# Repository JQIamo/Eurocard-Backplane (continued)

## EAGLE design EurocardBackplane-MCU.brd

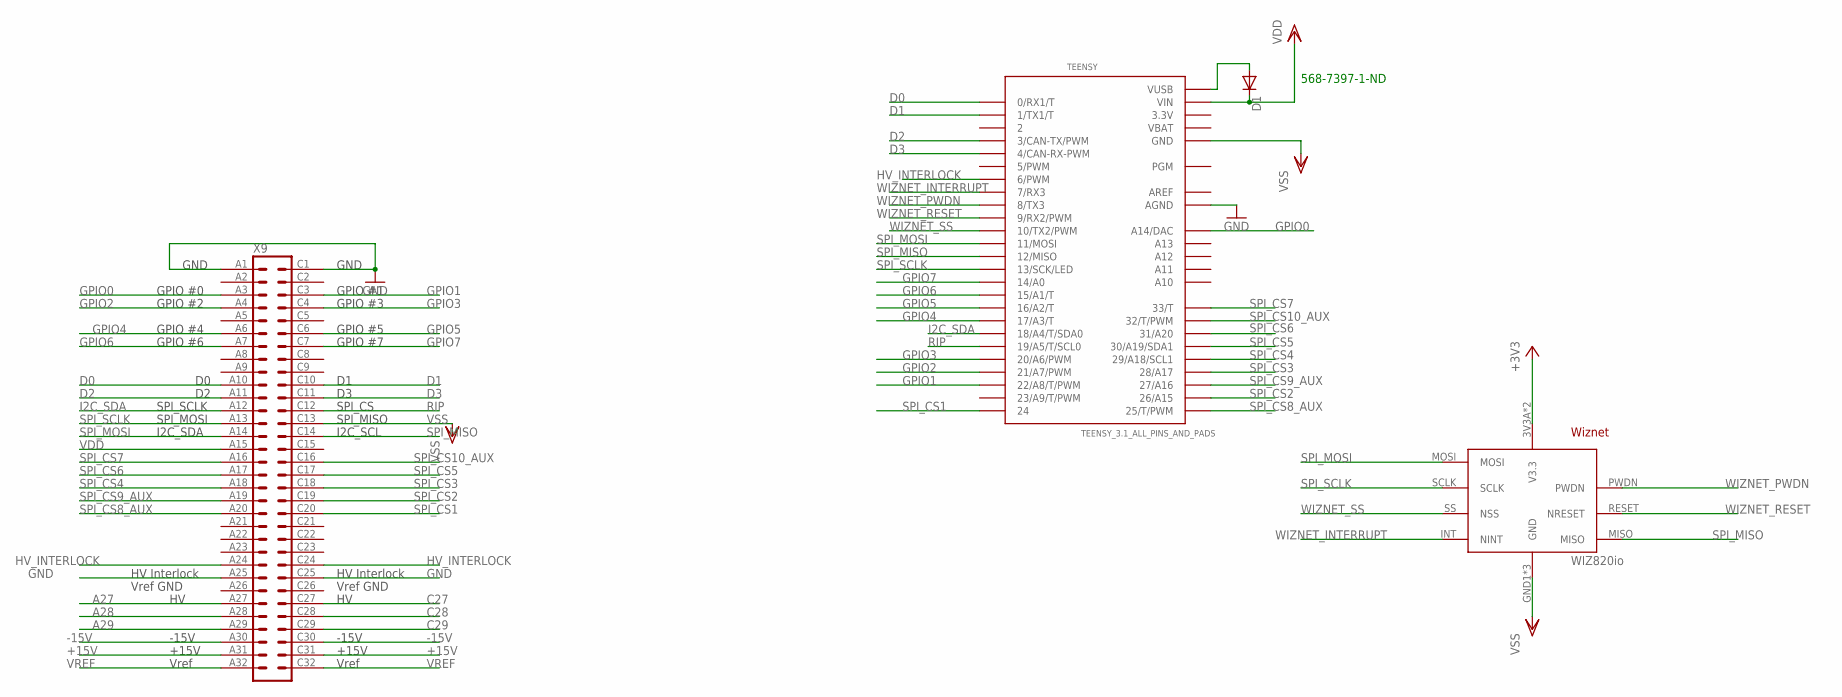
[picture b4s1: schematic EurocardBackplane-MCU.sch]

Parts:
D1: DIODE-SOD523; SOD523
TEENSY: TEENSY_3.1_ALL_PINS_AND_PADS; TEENSY_3.1_ALLPINS
U2: WIZ820IO; WIZNET
X9: VG64-PLAIN

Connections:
3.3V: TEENSY.3.3V, TEENSY.3.3V1 (3.3V), TEENSY.3.3V2 (3.3V)
+3V3: U2.3V3A (V3.3), U2.3V3B (V3.3)
+15V: X9.A31, X9.C31
-15V: X9.A30, X9.C30
A27: X9.A27
A28: X9.A28
A29: X9.A29
AREF: TEENSY.AREF
C27: X9.C27
C28: X9.C28
C29: X9.C29
D0: TEENSY.0 (0/RX1/T), X9.A10
D1: TEENSY.1 (1/TX1/T), X9.C10
D2: TEENSY.3 (3/CAN-TX/PWM), X9.A11
D3: TEENSY.4 (4/CAN-RX-PWM), X9.C11
GND: TEENSY.AGND, X9.A1, X9.A25, X9.C1, X9.C25
GPIO0: TEENSY.A14 (A14/DAC), X9.A3
GPIO1: TEENSY.22/A8 (22/A8/T/PWM), X9.C3
GPIO2: TEENSY.21/A7 (21/A7/PWM), X9.A4
GPIO3: TEENSY.20/A6 (20/A6/PWM), X9.C4
GPIO4: TEENSY.17/A3 (17/A3/T), X9.A6
GPIO5: TEENSY.16/A2 (16/A2/T), X9.C6
GPIO6: TEENSY.15/A1 (15/A1/T), X9.A7
GPIO7: TEENSY.14/A0, X9.C7
HV_INTERLOCK: TEENSY.6 (6/PWM), X9.A24, X9.C24
I2C_SDA: TEENSY.18/A4 (18/A4/T/SDA0), X9.A12
unnamed: D1.A, TEENSY.VUSB
RIP: TEENSY.19/A5 (19/A5/T/SCL0), X9.C12
SPI_CS1: TEENSY.24, X9.C20
SPI_CS2: TEENSY.26 (26/A15), X9.C19
SPI_CS3: TEENSY.28 (28/A17), X9.C18
SPI_CS4: TEENSY.29 (29/A18/SCL1), X9.A18
SPI_CS5: TEENSY.30 (30/A19/SDA1), X9.C17
SPI_CS6: TEENSY.31 (31/A20), X9.A17
SPI_CS7: TEENSY.33 (33/T), X9.A16
SPI_CS8_AUX: TEENSY.25 (25/T/PWM), X9.A20
SPI_CS9_AUX: TEENSY.27 (27/A16), X9.A19
SPI_CS10_AUX: TEENSY.32 (32/T/PWM), X9.C16
SPI_MISO: TEENSY.12 (12/MISO), U2.MISO, X9.C14
SPI_MOSI: TEENSY.11 (11/MOSI), U2.MOSI, X9.A14
SPI_SCLK: TEENSY.13 (13/SCK/LED), U2.SCLK, X9.A13
VBAT: TEENSY.VBAT
VDD: D1.C, TEENSY.VIN, X9.A15
VREF: X9.A32, X9.C32
VSS: TEENSY.GND, TEENSY.GND1 (GND), TEENSY.GND2 (GND), U2.GND1 (GND), U2.GND2 (GND), U2.GND3 (GND), X9.C13
WIZNET_INTERRUPT: TEENSY.7 (7/RX3), U2.INT (NINT)
WIZNET_PWDN: TEENSY.8 (8/TX3), U2.PWDN
WIZNET_RESET: TEENSY.9 (9/RX2/PWM), U2.RESET (NRESET)
WIZNET_SS: TEENSY.10 (10/TX2/PWM), U2.SS (NSS)

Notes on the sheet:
568-7397-1-ND

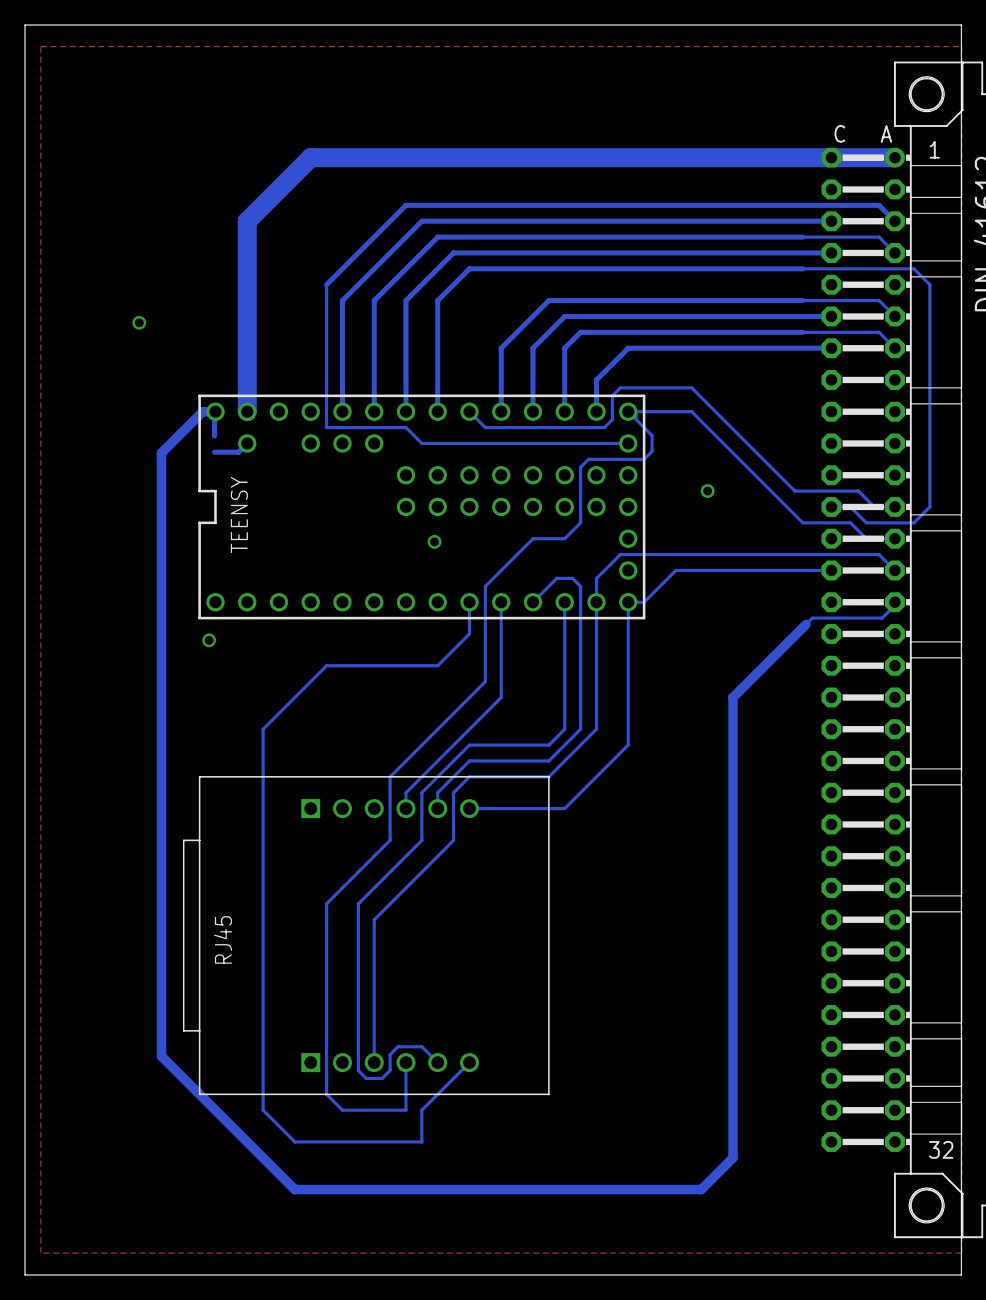
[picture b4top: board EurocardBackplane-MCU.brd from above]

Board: 2 copper layers, 74.9 x 100.0 mm, 4 parts (1 on the bottom side), 41 nets.

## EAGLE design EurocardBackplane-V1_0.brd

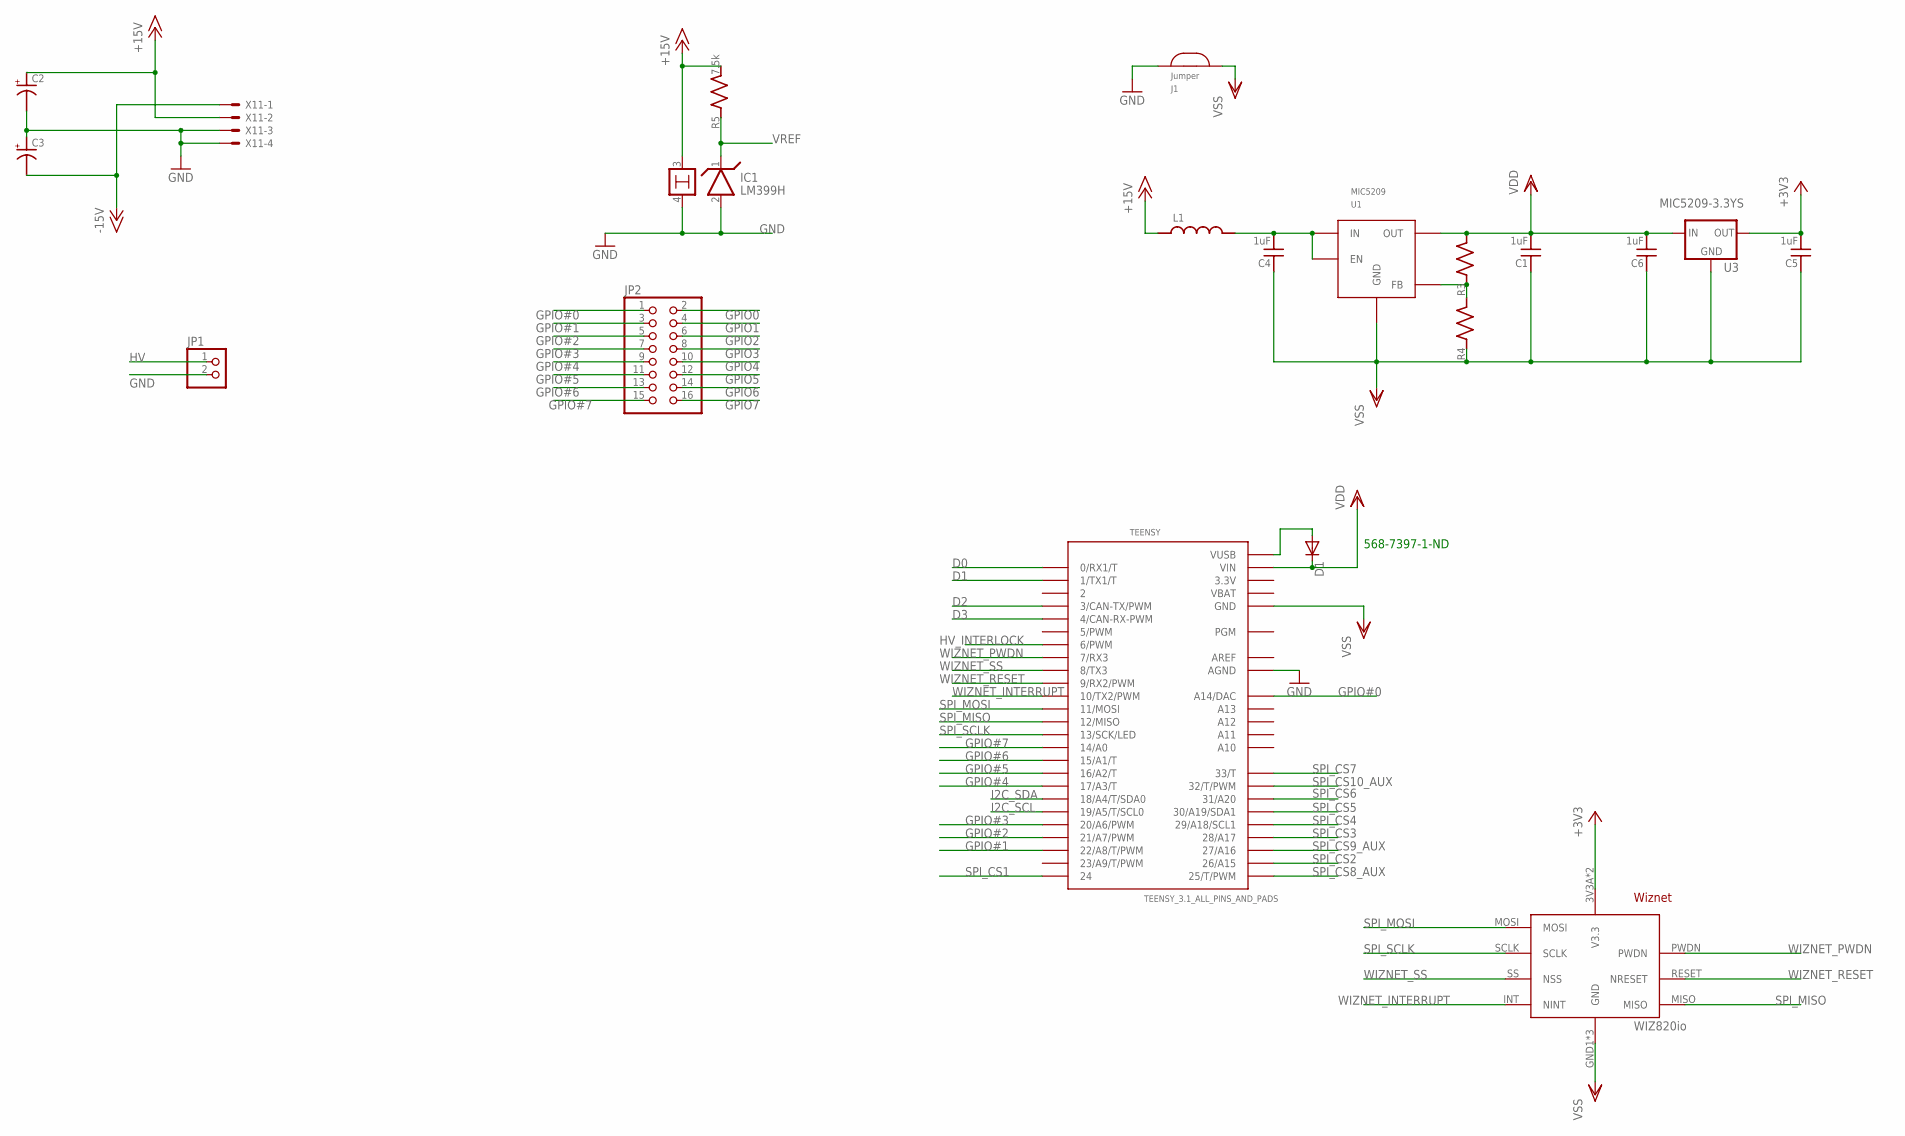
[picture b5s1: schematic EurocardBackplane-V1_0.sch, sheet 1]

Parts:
C1, C4, C5, C6: 1uF; C_MLCC_0603
C2, C3: C_POL_SMDF; PANASONIC_F
D1: DIODE-SOD523; SOD523
IC1: LM399H; TO39/4
J1: JUMPER; JUMP
JP1: PINHD-1X2; 1X02
JP2: PINHD-2X8; 2X08
L1: L_FERRITE_SMDLFERRITE_0805; R_0805
R3, R4: R_SMDR0603; R_0603
R5: 7.5k; R_0603
TEENSY: TEENSY_3.1_ALL_PINS_AND_PADS; TEENSY_3.1_ALLPINS
U1: MIC5209; TO263-5
U2: WIZ820IO; WIZNET
U3: MIC5209-3.3YS; SOT223-S
X11: 5566-4

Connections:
3.3V: TEENSY.3.3V, TEENSY.3.3V1 (3.3V), TEENSY.3.3V2 (3.3V)
+3V3: C5.P$2 (2), U2.3V3A (V3.3), U2.3V3B (V3.3), U3.3 (OUT)
+15V: C2.+, IC1.3, L1.P$1 (1), R5.P$2 (2), X11.2; also elsewhere on the board
-15V: C3.-, X11.1; also elsewhere on the board
AREF: TEENSY.AREF
D0: TEENSY.0 (0/RX1/T); also elsewhere on the board
D1: TEENSY.1 (1/TX1/T); also elsewhere on the board
D2: TEENSY.3 (3/CAN-TX/PWM); also elsewhere on the board
D3: TEENSY.4 (4/CAN-RX-PWM); also elsewhere on the board
GND: C2.-, C3.+, IC1.2, IC1.4, J1.P$2, JP1.2, TEENSY.AGND, X11.3, X11.4; also elsewhere on the board
GPIO0: JP2.2; also elsewhere on the board
GPIO1: JP2.4; also elsewhere on the board
GPIO2: JP2.6; also elsewhere on the board
GPIO3: JP2.8; also elsewhere on the board
GPIO4: JP2.10; also elsewhere on the board
GPIO5: JP2.12; also elsewhere on the board
GPIO6: JP2.14; also elsewhere on the board
GPIO7: JP2.16; also elsewhere on the board
GPIO#0: JP2.1, TEENSY.A14 (A14/DAC)
GPIO#1: JP2.3, TEENSY.22/A8 (22/A8/T/PWM)
GPIO#2: JP2.5, TEENSY.21/A7 (21/A7/PWM)
GPIO#3: JP2.7, TEENSY.20/A6 (20/A6/PWM)
GPIO#4: JP2.9, TEENSY.17/A3 (17/A3/T)
GPIO#5: JP2.11, TEENSY.16/A2 (16/A2/T)
GPIO#6: JP2.13, TEENSY.15/A1 (15/A1/T)
GPIO#7: JP2.15, TEENSY.14/A0
HV: JP1.1; also elsewhere on the board
HV_INTERLOCK: TEENSY.6 (6/PWM); also elsewhere on the board
I2C_SCL: TEENSY.19/A5 (19/A5/T/SCL0); also elsewhere on the board
I2C_SDA: TEENSY.18/A4 (18/A4/T/SDA0); also elsewhere on the board
unnamed: C4.P$2 (2), L1.P$2 (2), U1.1 (EN), U1.2 (IN)
unnamed: D1.A, TEENSY.VUSB
unnamed: R3.P$1 (1), R4.P$2 (2), U1.5 (FB)
SPI_CS1: TEENSY.24; also elsewhere on the board
SPI_CS2: TEENSY.26 (26/A15); also elsewhere on the board
SPI_CS3: TEENSY.28 (28/A17); also elsewhere on the board
SPI_CS4: TEENSY.29 (29/A18/SCL1); also elsewhere on the board
SPI_CS5: TEENSY.30 (30/A19/SDA1); also elsewhere on the board
SPI_CS6: TEENSY.31 (31/A20); also elsewhere on the board
SPI_CS7: TEENSY.33 (33/T); also elsewhere on the board
SPI_CS8_AUX: TEENSY.25 (25/T/PWM); also elsewhere on the board
SPI_CS9_AUX: TEENSY.27 (27/A16); also elsewhere on the board
SPI_CS10_AUX: TEENSY.32 (32/T/PWM); also elsewhere on the board
SPI_MISO: TEENSY.12 (12/MISO), U2.MISO; also elsewhere on the board
SPI_MOSI: TEENSY.11 (11/MOSI), U2.MOSI; also elsewhere on the board
SPI_SCLK: TEENSY.13 (13/SCK/LED), U2.SCLK; also elsewhere on the board
VBAT: TEENSY.VBAT
VDD: C1.P$2 (2), C6.P$2 (2), D1.C, R3.P$2 (2), TEENSY.VIN, U1.4 (OUT), U3.1 (IN)
VREF: IC1.1, R5.P$1 (1); also elsewhere on the board
VSS: C1.P$1 (1), C4.P$1 (1), C5.P$1 (1), C6.P$1 (1), J1.P$1, R4.P$1 (1), TEENSY.GND, TEENSY.GND1 (GND), TEENSY.GND2 (GND), U1.3 (GND), U1.6 (GND), U2.GND1 (GND), U2.GND2 (GND), U2.GND3 (GND), U3.2 (GND), U3.4 (GND)
WIZNET_INTERRUPT: TEENSY.10 (10/TX2/PWM), U2.INT (NINT)
WIZNET_PWDN: TEENSY.7 (7/RX3), U2.PWDN
WIZNET_RESET: TEENSY.9 (9/RX2/PWM), U2.RESET (NRESET)
WIZNET_SS: TEENSY.8 (8/TX3), U2.SS (NSS)

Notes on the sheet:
568-7397-1-ND

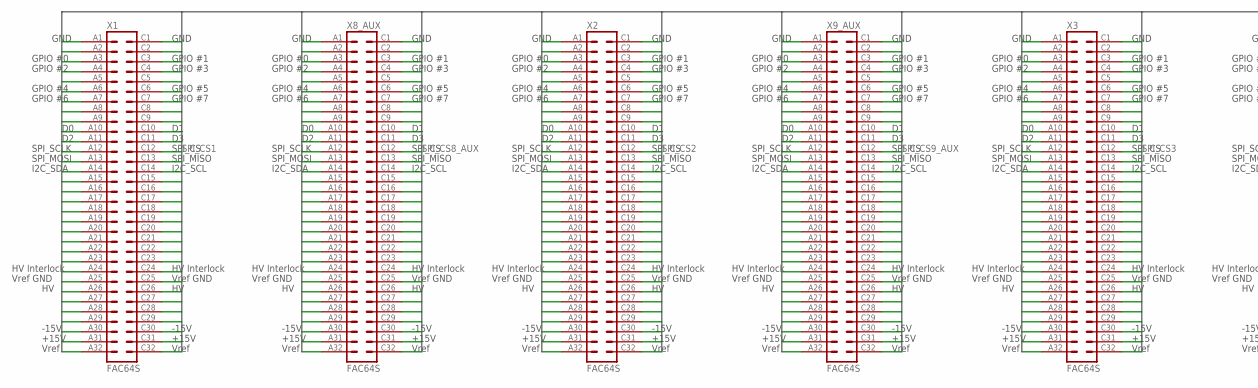
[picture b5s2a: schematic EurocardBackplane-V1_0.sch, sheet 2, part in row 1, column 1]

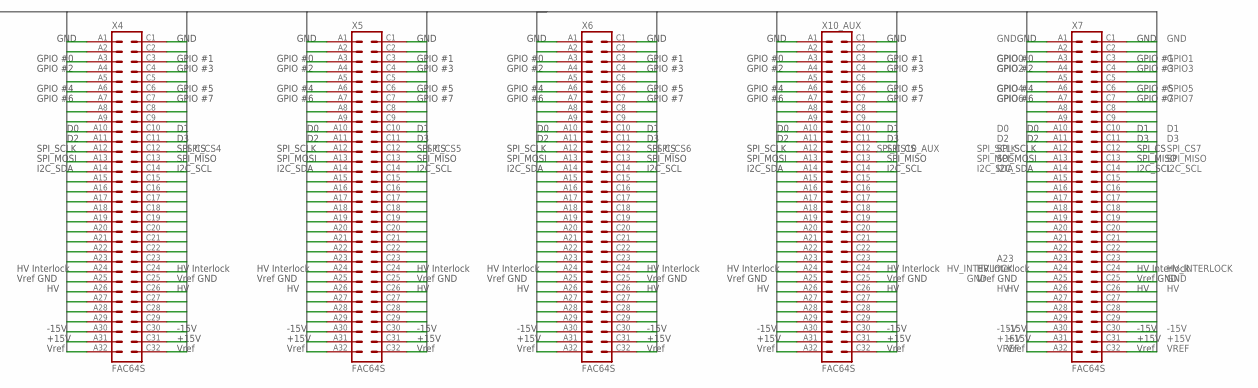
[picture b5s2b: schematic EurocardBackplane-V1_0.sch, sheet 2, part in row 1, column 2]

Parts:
X1, X2, X3, X4, X5, X6, X7, X8_AUX, X9_AUX, X10_AUX: FAC64S

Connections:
+15V: X1.A31, X1.C31, X2.A31, X2.C31, X3.A31, X3.C31, X4.A31, X4.C31, X5.A31, X5.C31, X6.A31, X6.C31, X7.A31, X7.C31, X8_AUX.A31, X8_AUX.C31, X9_AUX.A31, X9_AUX.C31, X10_AUX.A31, X10_AUX.C31; also elsewhere on the board
-15V: X1.A30, X1.C30, X2.A30, X2.C30, X3.A30, X3.C30, X4.A30, X4.C30, X5.A30, X5.C30, X6.A30, X6.C30, X7.A30, X7.C30, X8_AUX.A30, X8_AUX.C30, X9_AUX.A30, X9_AUX.C30, X10_AUX.A30, X10_AUX.C30; also elsewhere on the board
A2: X1.A2, X2.A2, X3.A2, X4.A2, X5.A2, X6.A2, X7.A2, X8_AUX.A2, X9_AUX.A2, X10_AUX.A2
A5: X1.A5, X2.A5, X3.A5, X4.A5, X5.A5, X6.A5, X7.A5, X8_AUX.A5, X9_AUX.A5, X10_AUX.A5
A8: X1.A8, X2.A8, X3.A8, X4.A8, X5.A8, X6.A8, X7.A8, X8_AUX.A8, X9_AUX.A8, X10_AUX.A8
A9: X1.A9, X2.A9, X3.A9, X4.A9, X5.A9, X6.A9, X7.A9, X8_AUX.A9, X9_AUX.A9, X10_AUX.A9
A15: X1.A15, X2.A15, X3.A15, X4.A15, X5.A15, X6.A15, X7.A15, X8_AUX.A15, X9_AUX.A15, X10_AUX.A15
A16: X1.A16, X2.A16, X3.A16, X4.A16, X5.A16, X6.A16, X7.A16, X8_AUX.A16, X9_AUX.A16, X10_AUX.A16
A17: X1.A17, X2.A17, X3.A17, X4.A17, X5.A17, X6.A17, X7.A17, X8_AUX.A17, X9_AUX.A17, X10_AUX.A17
A18: X1.A18, X2.A18, X3.A18, X4.A18, X5.A18, X6.A18, X7.A18, X8_AUX.A18, X9_AUX.A18, X10_AUX.A18
A19: X1.A19, X2.A19, X3.A19, X4.A19, X5.A19, X6.A19, X7.A19, X8_AUX.A19, X9_AUX.A19, X10_AUX.A19
A20: X1.A20, X2.A20, X3.A20, X4.A20, X5.A20, X6.A20, X7.A20, X8_AUX.A20, X9_AUX.A20, X10_AUX.A20
A21: X1.A21, X2.A21, X3.A21, X4.A21, X5.A21, X6.A21, X7.A21, X8_AUX.A21, X9_AUX.A21, X10_AUX.A21
A22: X1.A22, X2.A22, X3.A22, X4.A22, X5.A22, X6.A22, X7.A22, X8_AUX.A22, X9_AUX.A22, X10_AUX.A22
A23: X1.A23, X2.A23, X3.A23, X4.A23, X5.A23, X6.A23, X7.A23, X8_AUX.A23, X9_AUX.A23, X10_AUX.A23
A27: X1.A27, X2.A27, X3.A27, X4.A27, X5.A27, X6.A27, X7.A27, X8_AUX.A27, X9_AUX.A27, X10_AUX.A27
A28: X1.A28, X2.A28, X3.A28, X4.A28, X5.A28, X6.A28, X7.A28, X8_AUX.A28, X9_AUX.A28, X10_AUX.A28
A29: X1.A29, X2.A29, X3.A29, X4.A29, X5.A29, X6.A29, X7.A29, X8_AUX.A29, X9_AUX.A29, X10_AUX.A29
C2: X1.C2, X2.C2, X3.C2, X4.C2, X5.C2, X6.C2, X7.C2, X8_AUX.C2, X9_AUX.C2, X10_AUX.C2
C5: X1.C5, X2.C5, X3.C5, X4.C5, X5.C5, X6.C5, X7.C5, X8_AUX.C5, X9_AUX.C5, X10_AUX.C5
C8: X1.C8, X2.C8, X3.C8, X4.C8, X5.C8, X6.C8, X7.C8, X8_AUX.C8, X9_AUX.C8, X10_AUX.C8
C9: X1.C9, X2.C9, X3.C9, X4.C9, X5.C9, X6.C9, X7.C9, X8_AUX.C9, X9_AUX.C9, X10_AUX.C9
C15: X1.C15, X2.C15, X3.C15, X4.C15, X5.C15, X6.C15, X7.C15, X8_AUX.C15, X9_AUX.C15, X10_AUX.C15
C16: X1.C16, X2.C16, X3.C16, X4.C16, X5.C16, X6.C16, X7.C16, X8_AUX.C16, X9_AUX.C16, X10_AUX.C16
C17: X1.C17, X2.C17, X3.C17, X4.C17, X5.C17, X6.C17, X7.C17, X8_AUX.C17, X9_AUX.C17, X10_AUX.C17
C18: X1.C18, X2.C18, X3.C18, X4.C18, X5.C18, X6.C18, X7.C18, X8_AUX.C18, X9_AUX.C18, X10_AUX.C18
C19: X1.C19, X2.C19, X3.C19, X4.C19, X5.C19, X6.C19, X7.C19, X8_AUX.C19, X9_AUX.C19, X10_AUX.C19
C20: X1.C20, X2.C20, X3.C20, X4.C20, X5.C20, X6.C20, X7.C20, X8_AUX.C20, X9_AUX.C20, X10_AUX.C20
C21: X1.C21, X2.C21, X3.C21, X4.C21, X5.C21, X6.C21, X7.C21, X8_AUX.C21, X9_AUX.C21, X10_AUX.C21
C22: X1.C22, X2.C22, X3.C22, X4.C22, X5.C22, X6.C22, X7.C22, X8_AUX.C22, X9_AUX.C22, X10_AUX.C22
C23: X1.C23, X2.C23, X3.C23, X4.C23, X5.C23, X6.C23, X7.C23, X8_AUX.C23, X9_AUX.C23, X10_AUX.C23
C27: X1.C27, X2.C27, X3.C27, X4.C27, X5.C27, X6.C27, X7.C27, X8_AUX.C27, X9_AUX.C27, X10_AUX.C27
C28: X1.C28, X2.C28, X3.C28, X4.C28, X5.C28, X6.C28, X7.C28, X8_AUX.C28, X9_AUX.C28, X10_AUX.C28
C29: X1.C29, X2.C29, X3.C29, X4.C29, X5.C29, X6.C29, X7.C29, X8_AUX.C29, X9_AUX.C29, X10_AUX.C29
D0: X1.A10, X2.A10, X3.A10, X4.A10, X5.A10, X6.A10, X7.A10, X8_AUX.A10, X9_AUX.A10, X10_AUX.A10; also elsewhere on the board
D1: X1.C10, X2.C10, X3.C10, X4.C10, X5.C10, X6.C10, X7.C10, X8_AUX.C10, X9_AUX.C10, X10_AUX.C10; also elsewhere on the board
D2: X1.A11, X2.A11, X3.A11, X4.A11, X5.A11, X6.A11, X7.A11, X8_AUX.A11, X9_AUX.A11, X10_AUX.A11; also elsewhere on the board
D3: X1.C11, X2.C11, X3.C11, X4.C11, X5.C11, X6.C11, X7.C11, X8_AUX.C11, X9_AUX.C11, X10_AUX.C11; also elsewhere on the board
GND: X1.A1, X1.A25, X1.C1, X1.C25, X2.A1, X2.A25, X2.C1, X2.C25, X3.A1, X3.A25, X3.C1, X3.C25, X4.A1, X4.A25, X4.C1, X4.C25, X5.A1, X5.A25, X5.C1, X5.C25, X6.A1, X6.A25, X6.C1, X6.C25, X7.A1, X7.A25, X7.C1, X7.C25, X8_AUX.A1, X8_AUX.A25, X8_AUX.C1, X8_AUX.C25, X9_AUX.A1, X9_AUX.A25, X9_AUX.C1, X9_AUX.C25, X10_AUX.A1, X10_AUX.A25, X10_AUX.C1, X10_AUX.C25; also elsewhere on the board
GPIO0: X1.A3, X2.A3, X3.A3, X4.A3, X5.A3, X6.A3, X7.A3, X8_AUX.A3, X9_AUX.A3, X10_AUX.A3; also elsewhere on the board
GPIO1: X1.C3, X2.C3, X3.C3, X4.C3, X5.C3, X6.C3, X7.C3, X8_AUX.C3, X9_AUX.C3, X10_AUX.C3; also elsewhere on the board
GPIO2: X1.A4, X2.A4, X3.A4, X4.A4, X5.A4, X6.A4, X7.A4, X8_AUX.A4, X9_AUX.A4, X10_AUX.A4; also elsewhere on the board
GPIO3: X1.C4, X2.C4, X3.C4, X4.C4, X5.C4, X6.C4, X7.C4, X8_AUX.C4, X9_AUX.C4, X10_AUX.C4; also elsewhere on the board
GPIO4: X1.A6, X2.A6, X3.A6, X4.A6, X5.A6, X6.A6, X7.A6, X8_AUX.A6, X9_AUX.A6, X10_AUX.A6; also elsewhere on the board
GPIO5: X1.C6, X2.C6, X3.C6, X4.C6, X5.C6, X6.C6, X7.C6, X8_AUX.C6, X9_AUX.C6, X10_AUX.C6; also elsewhere on the board
GPIO6: X1.A7, X2.A7, X3.A7, X4.A7, X5.A7, X6.A7, X7.A7, X8_AUX.A7, X9_AUX.A7, X10_AUX.A7; also elsewhere on the board
GPIO7: X1.C7, X2.C7, X3.C7, X4.C7, X5.C7, X6.C7, X7.C7, X8_AUX.C7, X9_AUX.C7, X10_AUX.C7; also elsewhere on the board
HV: X1.A26, X1.C26, X2.A26, X2.C26, X3.A26, X3.C26, X4.A26, X4.C26, X5.A26, X5.C26, X6.A26, X6.C26, X7.A26, X7.C26, X8_AUX.A26, X8_AUX.C26, X9_AUX.A26, X9_AUX.C26, X10_AUX.A26, X10_AUX.C26; also elsewhere on the board
HV_INTERLOCK: X1.A24, X1.C24, X2.A24, X2.C24, X3.A24, X3.C24, X4.A24, X4.C24, X5.A24, X5.C24, X6.A24, X6.C24, X7.A24, X7.C24, X8_AUX.A24, X8_AUX.C24, X9_AUX.A24, X9_AUX.C24, X10_AUX.A24, X10_AUX.C24; also elsewhere on the board
I2C_SCL: X1.C14, X2.C14, X3.C14, X4.C14, X5.C14, X6.C14, X7.C14, X8_AUX.C14, X9_AUX.C14, X10_AUX.C14; also elsewhere on the board
I2C_SDA: X1.A14, X2.A14, X3.A14, X4.A14, X5.A14, X6.A14, X7.A14, X8_AUX.A14, X9_AUX.A14, X10_AUX.A14; also elsewhere on the board
SPI_CS1: X1.C12; also elsewhere on the board
SPI_CS2: X2.C12; also elsewhere on the board
SPI_CS3: X3.C12; also elsewhere on the board
SPI_CS4: X4.C12; also elsewhere on the board
SPI_CS5: X5.C12; also elsewhere on the board
SPI_CS6: X6.C12; also elsewhere on the board
SPI_CS7: X7.C12; also elsewhere on the board
SPI_CS8_AUX: X8_AUX.C12; also elsewhere on the board
SPI_CS9_AUX: X9_AUX.C12; also elsewhere on the board
SPI_CS10_AUX: X10_AUX.C12; also elsewhere on the board
SPI_MISO: X1.C13, X2.C13, X3.C13, X4.C13, X5.C13, X6.C13, X7.C13, X8_AUX.C13, X9_AUX.C13, X10_AUX.C13; also elsewhere on the board
SPI_MOSI: X1.A13, X2.A13, X3.A13, X4.A13, X5.A13, X6.A13, X7.A13, X8_AUX.A13, X9_AUX.A13, X10_AUX.A13; also elsewhere on the board
SPI_SCLK: X1.A12, X2.A12, X3.A12, X4.A12, X5.A12, X6.A12, X7.A12, X8_AUX.A12, X9_AUX.A12, X10_AUX.A12; also elsewhere on the board
VREF: X1.A32, X1.C32, X2.A32, X2.C32, X3.A32, X3.C32, X4.A32, X4.C32, X5.A32, X5.C32, X6.A32, X6.C32, X7.A32, X7.C32, X8_AUX.A32, X8_AUX.C32, X9_AUX.A32, X9_AUX.C32, X10_AUX.A32, X10_AUX.C32; also elsewhere on the board

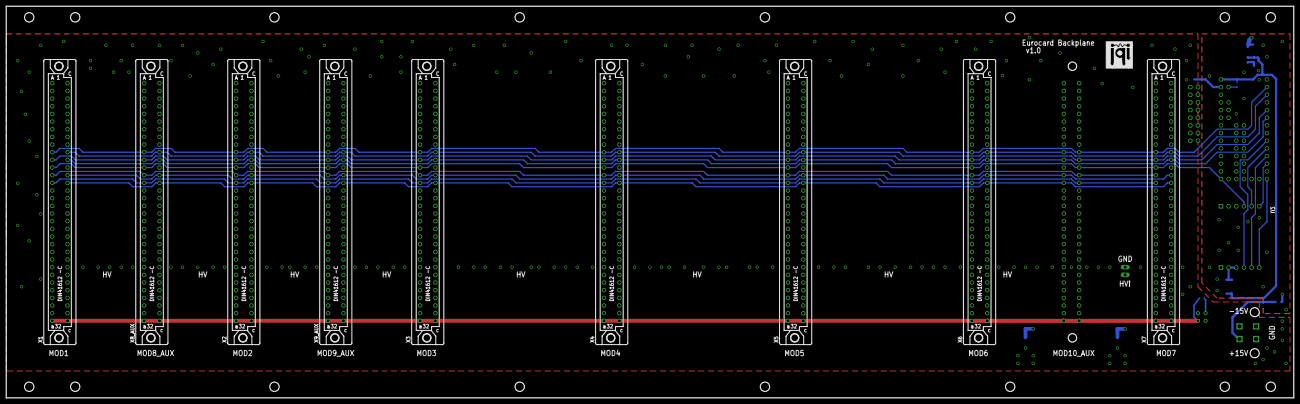
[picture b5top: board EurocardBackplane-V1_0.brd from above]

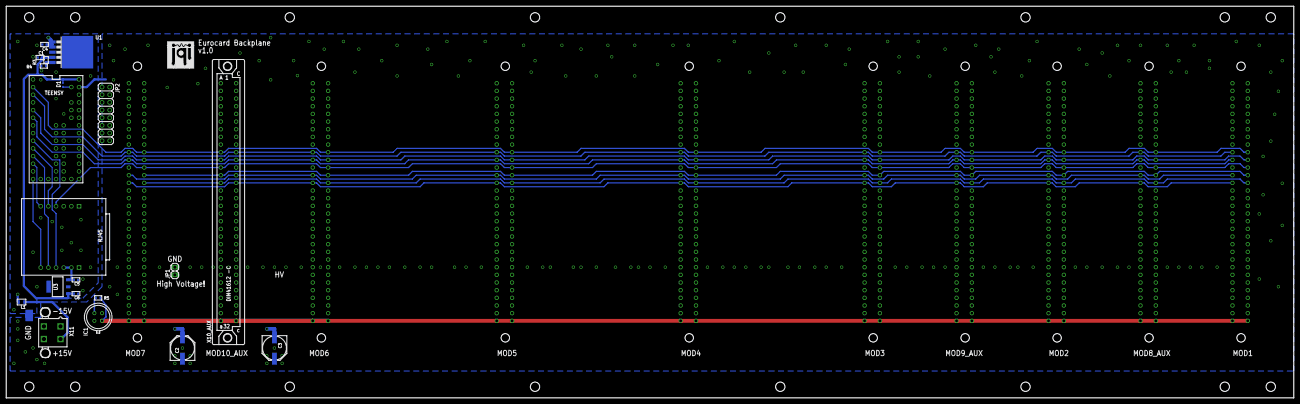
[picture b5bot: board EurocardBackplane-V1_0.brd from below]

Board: 4 copper layers, 426.7 x 129.8 mm, 33 parts (22 on the bottom side), 84 nets.

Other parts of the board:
U$1, U$4: JQI_LOGO_NEGATIVE-SILKSCREEN
U$3: BACKPLANE

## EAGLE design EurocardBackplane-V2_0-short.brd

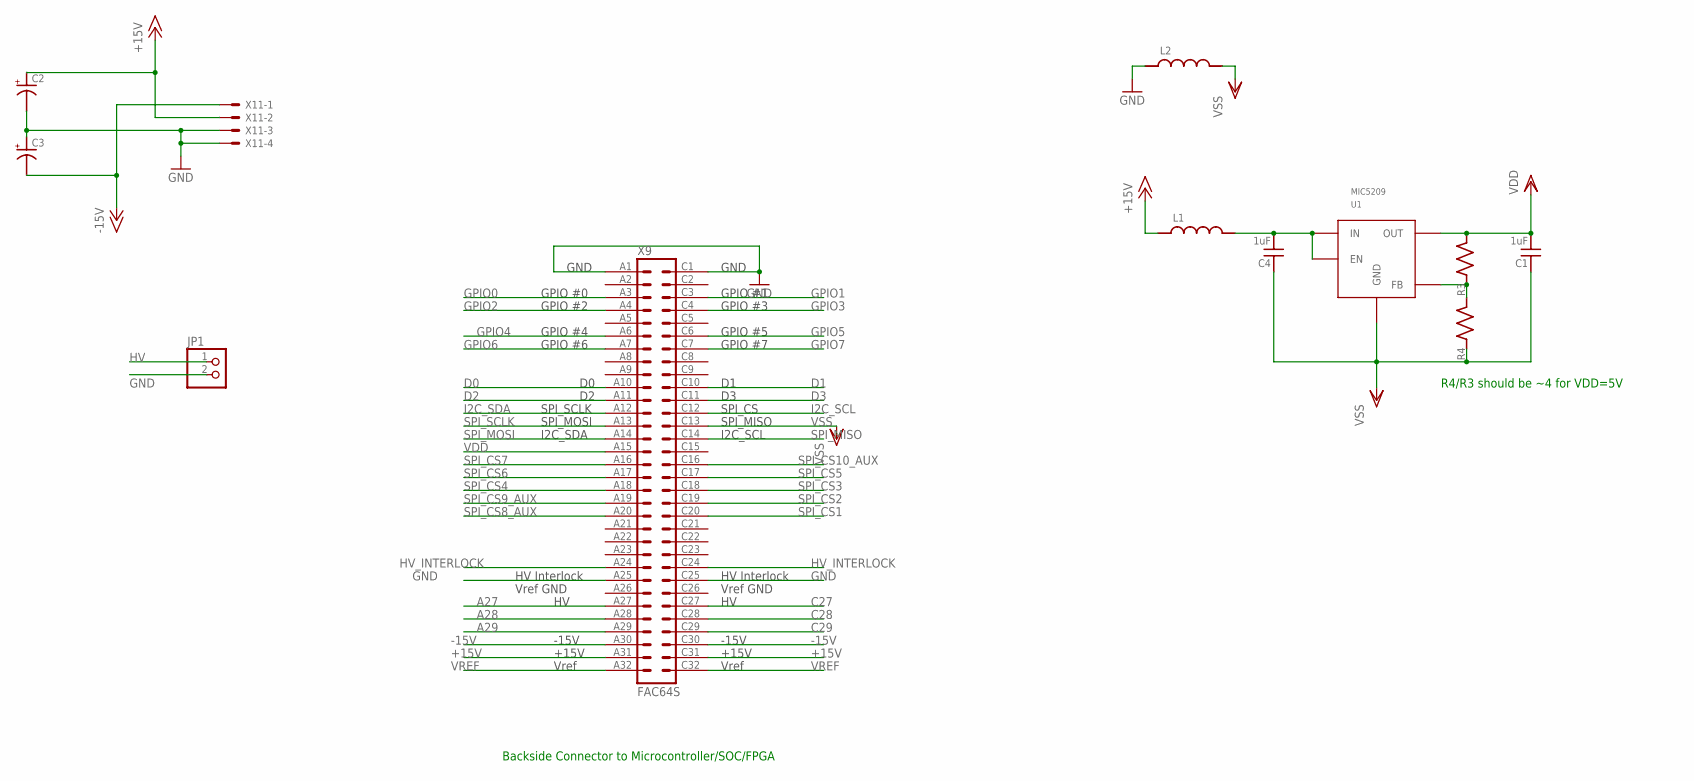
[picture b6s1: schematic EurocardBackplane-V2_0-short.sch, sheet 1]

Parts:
C1, C4: 1uF; C_MLCC_0603
C2, C3: C_POL_SMDF; PANASONIC_F
JP1: PINHD-1X2; 1X02
L1, L2: L_FERRITE_SMDLFERRITE_0805; R_0805
R3, R4: R_SMDR0603; R_0603
U1: MIC5209; TO263-5
X9: FAC64S
X11: 5566-4

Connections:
+15V: C2.+, L1.P$1 (1), X9.A31, X9.C31, X11.2; also elsewhere on the board
-15V: C3.-, X9.A30, X9.C30, X11.1; also elsewhere on the board
A27: X9.A27; also elsewhere on the board
A28: X9.A28; also elsewhere on the board
A29: X9.A29; also elsewhere on the board
C27: X9.C27; also elsewhere on the board
C28: X9.C28; also elsewhere on the board
C29: X9.C29; also elsewhere on the board
D0: X9.A10; also elsewhere on the board
D1: X9.C10; also elsewhere on the board
D2: X9.A11; also elsewhere on the board
D3: X9.C11; also elsewhere on the board
GND: C2.-, C3.+, JP1.2, L2.P$1 (1), X9.A1, X9.A25, X9.C1, X9.C25, X11.3, X11.4; also elsewhere on the board
GPIO0: X9.A3; also elsewhere on the board
GPIO1: X9.C3; also elsewhere on the board
GPIO2: X9.A4; also elsewhere on the board
GPIO3: X9.C4; also elsewhere on the board
GPIO4: X9.A6; also elsewhere on the board
GPIO5: X9.C6; also elsewhere on the board
GPIO6: X9.A7; also elsewhere on the board
GPIO7: X9.C7; also elsewhere on the board
HV: JP1.1; also elsewhere on the board
HV_INTERLOCK: X9.A24, X9.C24; also elsewhere on the board
I2C_SCL: X9.C12; also elsewhere on the board
I2C_SDA: X9.A12; also elsewhere on the board
unnamed: C4.P$2 (2), L1.P$2 (2), U1.1 (EN), U1.2 (IN)
unnamed: R3.P$1 (1), R4.P$2 (2), U1.5 (FB)
SPI_CS1: X9.C20
SPI_CS2: X9.C19
SPI_CS3: X9.C18
SPI_CS4: X9.A18
SPI_CS5: X9.C17
SPI_CS6: X9.A17; also elsewhere on the board
SPI_CS7: X9.A16; also elsewhere on the board
SPI_CS8_AUX: X9.A20
SPI_CS9_AUX: X9.A19
SPI_CS10_AUX: X9.C16; also elsewhere on the board
SPI_MISO: X9.C14; also elsewhere on the board
SPI_MOSI: X9.A14; also elsewhere on the board
SPI_SCLK: X9.A13; also elsewhere on the board
VDD: C1.P$2 (2), R3.P$2 (2), U1.4 (OUT), X9.A15; also elsewhere on the board
VREF: X9.A32, X9.C32; also elsewhere on the board
VSS: C1.P$1 (1), C4.P$1 (1), L2.P$2 (2), R4.P$1 (1), U1.3 (GND), U1.6 (GND), X9.C13; also elsewhere on the board

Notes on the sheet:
Backside Connector to Microcontroller/SOC/FPGA
R4/R3 should be ~4 for VDD=5V

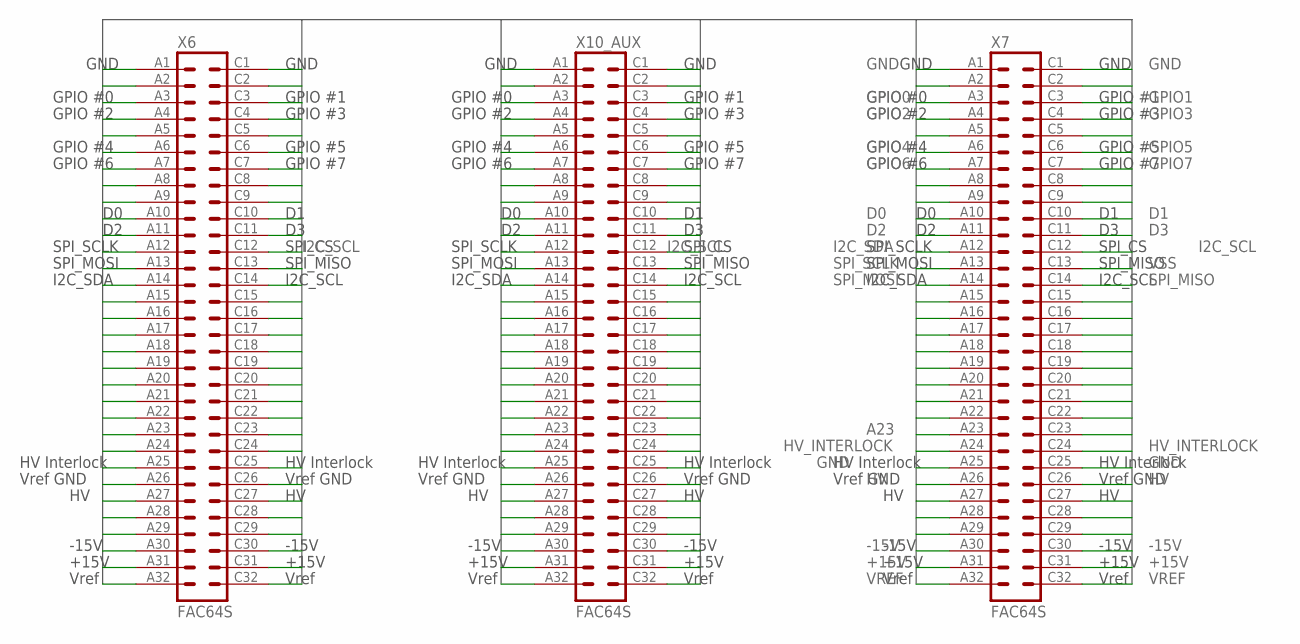
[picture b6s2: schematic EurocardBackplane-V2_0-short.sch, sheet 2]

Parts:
X6, X7, X10_AUX: FAC64S

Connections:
+15V: X6.A31, X6.C31, X7.A31, X7.C31, X10_AUX.A31, X10_AUX.C31; also elsewhere on the board
-15V: X6.A30, X6.C30, X7.A30, X7.C30, X10_AUX.A30, X10_AUX.C30; also elsewhere on the board
A2: X6.A2, X7.A2, X10_AUX.A2
A5: X6.A5, X7.A5, X10_AUX.A5
A8: X6.A8, X7.A8, X10_AUX.A8
A9: X6.A9, X7.A9, X10_AUX.A9
A16: X6.A16, X7.A16, X10_AUX.A16
A17: X6.A17, X7.A17, X10_AUX.A17
A18: X6.A18, X7.A18, X10_AUX.A18
A19: X6.A19, X7.A19, X10_AUX.A19
A20: X6.A20, X7.A20, X10_AUX.A20
A21: X6.A21, X7.A21, X10_AUX.A21
A22: X6.A22, X7.A22, X10_AUX.A22
A23: X6.A23, X7.A23, X10_AUX.A23
A27: X6.A27, X7.A27, X10_AUX.A27; also elsewhere on the board
A28: X6.A28, X7.A28, X10_AUX.A28; also elsewhere on the board
A29: X6.A29, X7.A29, X10_AUX.A29; also elsewhere on the board
C2: X6.C2, X7.C2, X10_AUX.C2
C5: X6.C5, X7.C5, X10_AUX.C5
C8: X6.C8, X7.C8, X10_AUX.C8
C9: X6.C9, X7.C9, X10_AUX.C9
C16: X6.C16, X7.C16, X10_AUX.C16
C17: X6.C17, X7.C17, X10_AUX.C17
C18: X6.C18, X7.C18, X10_AUX.C18
C19: X6.C19, X7.C19, X10_AUX.C19
C20: X6.C20, X7.C20, X10_AUX.C20
C21: X6.C21, X7.C21, X10_AUX.C21
C22: X6.C22, X7.C22, X10_AUX.C22
C23: X6.C23, X7.C23, X10_AUX.C23
C27: X6.C27, X7.C27, X10_AUX.C27; also elsewhere on the board
C28: X6.C28, X7.C28, X10_AUX.C28; also elsewhere on the board
C29: X6.C29, X7.C29, X10_AUX.C29; also elsewhere on the board
D0: X6.A10, X7.A10, X10_AUX.A10; also elsewhere on the board
D1: X6.C10, X7.C10, X10_AUX.C10; also elsewhere on the board
D2: X6.A11, X7.A11, X10_AUX.A11; also elsewhere on the board
D3: X6.C11, X7.C11, X10_AUX.C11; also elsewhere on the board
GND: X6.A1, X6.A25, X6.C1, X6.C25, X7.A1, X7.A25, X7.C1, X7.C25, X10_AUX.A1, X10_AUX.A25, X10_AUX.C1, X10_AUX.C25; also elsewhere on the board
GPIO0: X6.A3, X7.A3, X10_AUX.A3; also elsewhere on the board
GPIO1: X6.C3, X7.C3, X10_AUX.C3; also elsewhere on the board
GPIO2: X6.A4, X7.A4, X10_AUX.A4; also elsewhere on the board
GPIO3: X6.C4, X7.C4, X10_AUX.C4; also elsewhere on the board
GPIO4: X6.A6, X7.A6, X10_AUX.A6; also elsewhere on the board
GPIO5: X6.C6, X7.C6, X10_AUX.C6; also elsewhere on the board
GPIO6: X6.A7, X7.A7, X10_AUX.A7; also elsewhere on the board
GPIO7: X6.C7, X7.C7, X10_AUX.C7; also elsewhere on the board
HV: X6.A26, X6.C26, X7.A26, X7.C26, X10_AUX.A26, X10_AUX.C26; also elsewhere on the board
HV_INTERLOCK: X6.A24, X6.C24, X7.A24, X7.C24, X10_AUX.A24, X10_AUX.C24; also elsewhere on the board
I2C_SCL: X6.C12, X7.C12, X10_AUX.C12; also elsewhere on the board
I2C_SDA: X6.A12, X7.A12, X10_AUX.A12; also elsewhere on the board
SPI_CS6: X6.C15; also elsewhere on the board
SPI_CS7: X7.C15; also elsewhere on the board
SPI_CS10_AUX: X10_AUX.C15; also elsewhere on the board
SPI_MISO: X6.C14, X7.C14, X10_AUX.C14; also elsewhere on the board
SPI_MOSI: X6.A14, X7.A14, X10_AUX.A14; also elsewhere on the board
SPI_SCLK: X6.A13, X7.A13, X10_AUX.A13; also elsewhere on the board
VDD: X6.A15, X7.A15, X10_AUX.A15; also elsewhere on the board
VREF: X6.A32, X6.C32, X7.A32, X7.C32, X10_AUX.A32, X10_AUX.C32; also elsewhere on the board
VSS: X6.C13, X7.C13, X10_AUX.C13; also elsewhere on the board
